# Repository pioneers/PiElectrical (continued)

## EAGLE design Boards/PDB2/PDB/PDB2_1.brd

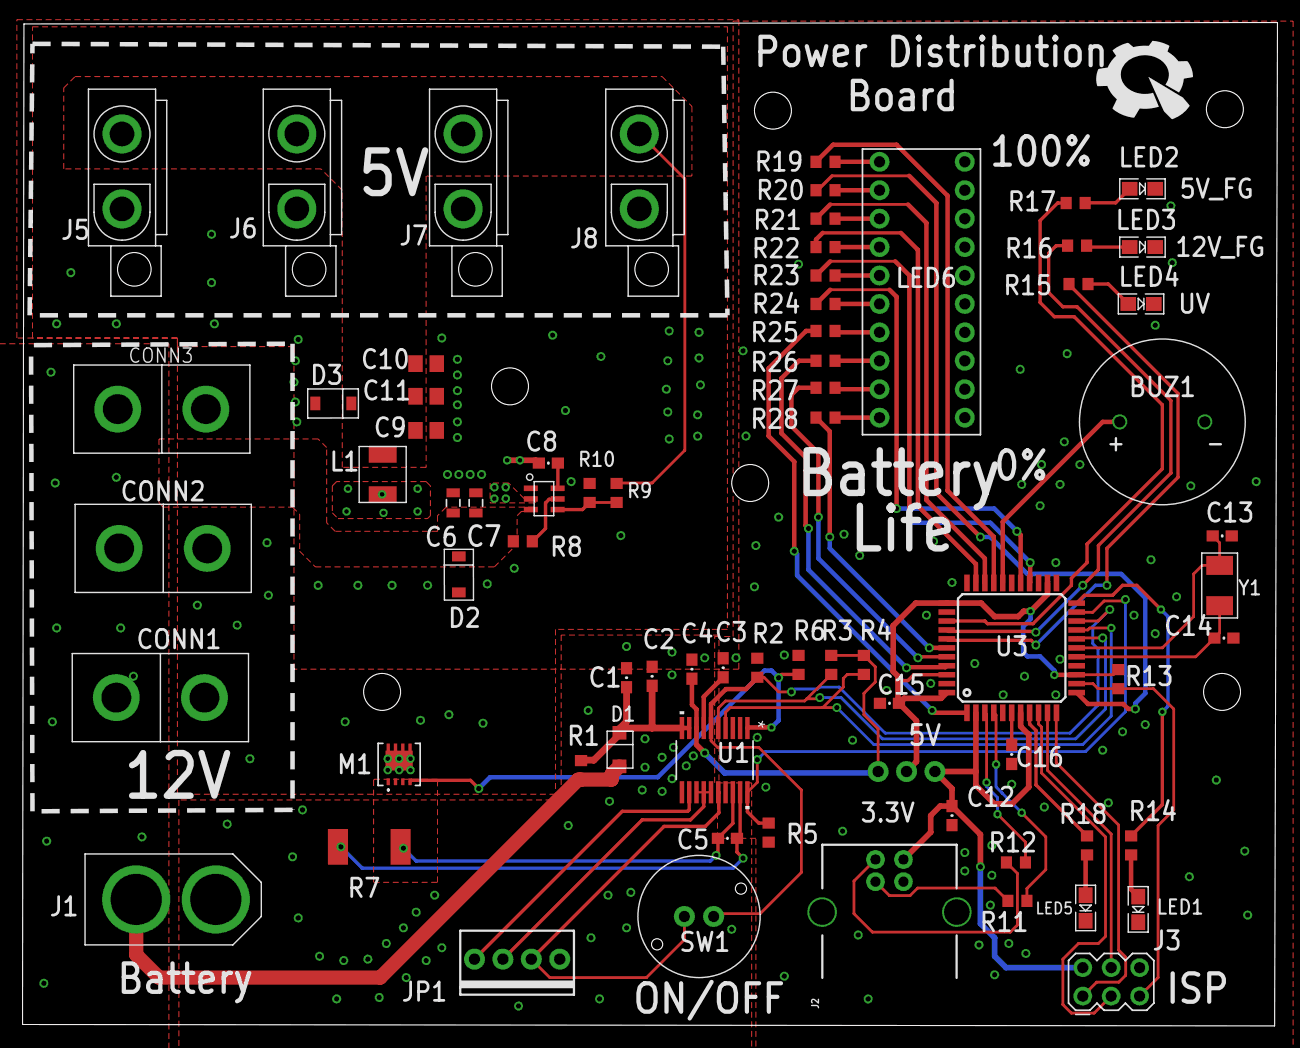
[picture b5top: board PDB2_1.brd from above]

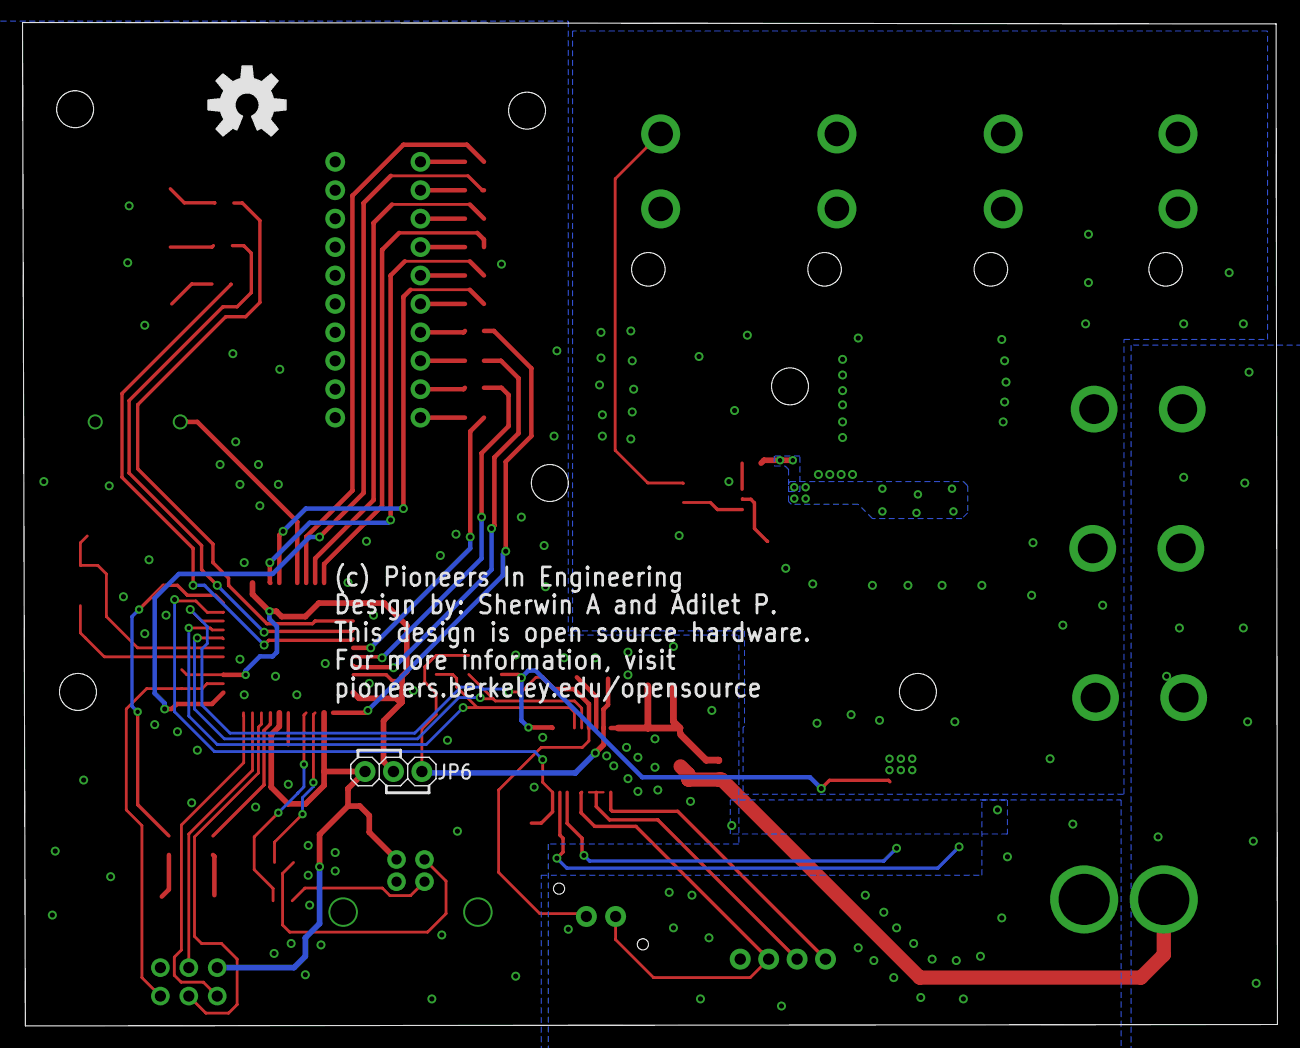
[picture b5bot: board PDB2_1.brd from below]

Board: 2 copper layers, 112.1 x 89.7 mm, 81 parts (2 on the bottom side), 64 nets.

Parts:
BUZ1: BUZZER_3.3V
C1, C2, C3, C4, C12, C15, C16: 2.2uF; 0603-CAP
C5, C8: .1uF; 0603-CAP
C6, C7: 22uF; 0805
C9, C10, C11: 22uF; C0805
C13, C14: 18pF; 0603-CAP
CONN1, CONN2, CONN3: ANDERSONVERTICAL; ANDERSON_VERTICAL
D1: D_NRVB120VLSFT1G; ON_SEMI_SOD-123F
D2, D3: BZT52C2VXX_ZENER; SOD-123
J1: XT60CONNECTOR
J2: USB_B_PTH; USB-B-PTH
J3: AVR_SPI_PRG_6MA03-2; MA03-2
JP1: 1X04-MTA
JP2, JP3, JP4, JP5: ATX
JP6: 1X03-JMP-OPTION
L1: 3.3uH; MWSA0402S
LED1, LED2, LED3, LED4, LED5: LED-0805
LED6: BAR_SEGMENT_DISPLAY
M1: CSD17577Q3A; DNH0008A
R1, R2, R8, R10, R13: 10k; R0603
R3, R4: 3.3k; R0603
R5, R6: 100k; R0603
R7: 5m; R2512
R9: 56.2k; R0603
R11, R12: 22R; R0603
R14, R15, R16, R17, R18: 330R; R0603
R19, R20, R21, R22, R23, R24, R25, R26, R27, R28: 220R; R0603
STANDOFF1, STANDOFF2, STANDOFF3, STANDOFF4, STANDOFF5, STANDOFF6: STAND-OFFTIGHT; STAND-OFF-TIGHT
SW1: PUSH_BUTTON; BUTTON_K12A
U1: BQ7692006PWRPW20-M; PW20-M
U2: SOT-23_6PIN_COPY
U3: ATMEGA32U4-AU; TQFP44
U$1: PIE-LOGO-SMALL
U$2: OSHW-LOGO-L
Y1: 8MHZ_X50328MSB2GI; SMD-5032_2P

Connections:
3.3V: C4.2, JP6.1, R3.2, R4.2, U1.8
5V: C9.1, C10.1, C11.1, D3.N, JP2.P$1, JP3.P$1, JP4.P$1, JP5.P$1, L1.P$1, R9.2
12V: C6.2, C7.2, CONN1.PIN1, CONN2.PIN2, CONN3.PIN2, D1.P, D2.N, J1.12V, R1.2, R8.1, U2.P$3
ALERT: R5.1, U1.20, U3.21
BCELL1: JP1.2, SW1.P$1, U1.16
BCELL2: JP1.3, U1.13, U1.14, U1.15
BCELL3: JP1.4, U1.12
BOOT: R2.2, SW1.P$2, U1.6, U3.20
BST: C8.1, U2.P$6
BUZZ: BUZ1.P1, U3.29
CAP1: C3.2, U1.7
D+: J2.D+, R11.1
D-: J2.D-, R12.1
DSG: M1.4, R6.2, U1.1
EN/MISO: J3.1, U3.11
FB: R9.1, R10.2, U2.P$4
GND: BUZ1.P2, C1.1, C2.1, C3.1, C4.1, C5.2, C12.1, C13.1, C14.1, C15.1, C16.1, J1.GND, J2.GND, J2.SHLD1, J2.SHLD2, J3.6, JP1.1, LED1.C, LED2.C, LED3.C, LED4.C, LED5.C, LED6.BAR_DISPLAY10, LED6.BAR_DISPLAY11, LED6.BAR_DISPLAY12, LED6.BAR_DISPLAY13, LED6.BAR_DISPLAY14, LED6.BAR_DISPLAY15, LED6.BAR_DISPLAY16, LED6.BAR_DISPLAY17, LED6.BAR_DISPLAY18, LED6.BAR_DISPLAY19, R2.1, R5.2, R6.1, R7.2, U1.3, U1.17, U1.19, U3.5, U3.15, U3.23, U3.33, U3.35, U3.43
GND_OUT: C6.1, C7.1, C9.2, C10.2, C11.2, CONN1.PIN2, CONN2.PIN1, CONN3.PIN1, D2.P, D3.P, JP2.P$2, JP3.P$2, JP4.P$2, JP5.P$2, M1.5, M1.6, M1.7, M1.8, M1.9, R10.1, U2.P$1
LED1: R28.1, U3.39
LED2: R27.1, U3.40
LED3: R26.1, U3.41
LED4: R25.1, U3.1
LED5: R24.1, U3.27
LED6: R23.1, U3.26
LED7: R22.1, U3.32
LED8: R21.1, U3.31
LED9: R20.1, U3.12
LED10: R19.1, U3.30
MOSI: J3.4, U3.10
unnamed: C13.2, U3.17, Y1.P$2
unnamed: R12.2, U3.3
unnamed: R11.2, U3.4
unnamed: C14.2, U3.16, Y1.P$1
unnamed: C16.2, U3.6
unnamed: LED6.BAR_DISPLAY0, R19.2
unnamed: LED6.BAR_DISPLAY1, R20.2
unnamed: LED6.BAR_DISPLAY2, R21.2
unnamed: LED6.BAR_DISPLAY3, R22.2
unnamed: LED6.BAR_DISPLAY4, R23.2
unnamed: LED6.BAR_DISPLAY5, R24.2
unnamed: LED6.BAR_DISPLAY6, R25.2
unnamed: LED6.BAR_DISPLAY7, R26.2
unnamed: LED6.BAR_DISPLAY8, R27.2
unnamed: LED6.BAR_DISPLAY9, R28.2
unnamed: R18.1, U3.8
unnamed: LED5.A, R18.2
unnamed: LED1.A, R14.2
unnamed: R14.1, U3.22
unnamed: R8.2, U2.P$5
unnamed: R17.1, U3.36
unnamed: R16.1, U3.37
unnamed: R15.1, U3.38
unnamed: LED2.A, R17.2
unnamed: LED3.A, R16.2
unnamed: LED4.A, R15.2
RST: J3.5, R13.1, U3.13
SCL: R3.1, U1.5, U3.18
SCLK: J3.3, U3.9
SDA: R4.1, U1.4, U3.19
SRP: C5.1, M1.1, M1.2, M1.3, R7.1, U1.18
SW: C8.2, L1.P$2, U2.P$2
UVCC: C12.2, J2.VBUS, J3.2, JP6.3, U3.2, U3.7
VCC: C15.2, JP6.2, R13.2, U3.14, U3.24, U3.34, U3.42, U3.44
VIN: C1.2, C2.2, D1.N, R1.1, U1.9, U1.10

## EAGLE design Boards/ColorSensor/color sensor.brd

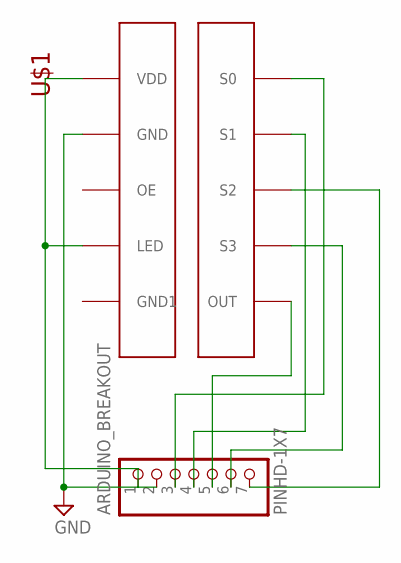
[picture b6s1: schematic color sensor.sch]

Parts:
ARDUINO_BREAKOUT: PINHD-1X7; 1X07
U$1: COLOR_SENSOR

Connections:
GND: ARDUINO_BREAKOUT.2, U$1.P9 (GND)
unnamed: ARDUINO_BREAKOUT.1, U$1.P7 (LED), U$1.P10 (VDD)
unnamed: ARDUINO_BREAKOUT.3, U$1.P5 (S0)
unnamed: ARDUINO_BREAKOUT.4, U$1.P4 (S1)
unnamed: ARDUINO_BREAKOUT.7, U$1.P3 (S2)
unnamed: ARDUINO_BREAKOUT.6, U$1.P2 (S3)
unnamed: ARDUINO_BREAKOUT.5, U$1.P1 (OUT)

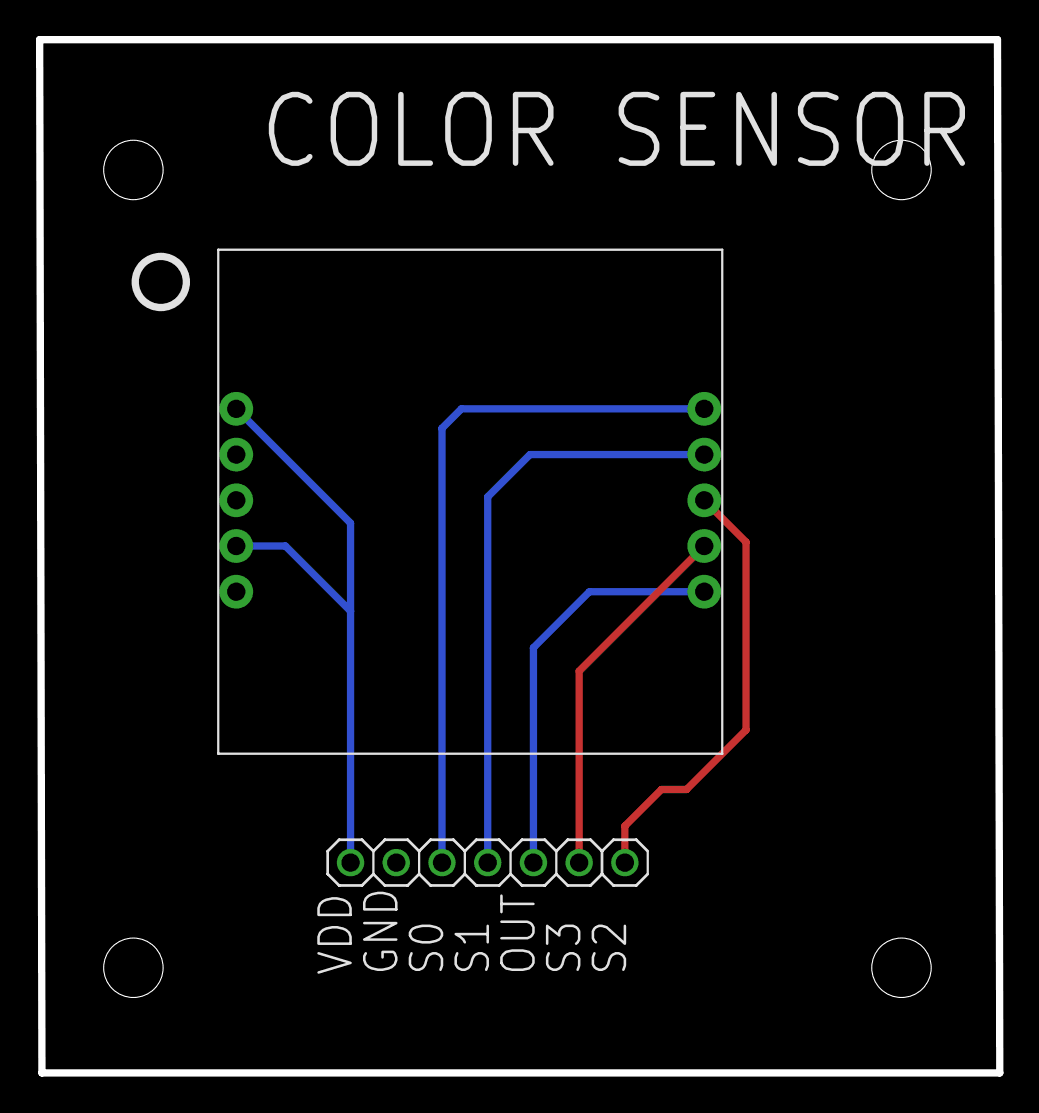
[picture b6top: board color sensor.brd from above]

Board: 2 copper layers, 53.3 x 57.4 mm, 7 parts (1 on the bottom side), 7 nets.

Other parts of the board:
U$2: PIE-LOGO
U$3, U$4, U$5, U$6: STAND-OFF

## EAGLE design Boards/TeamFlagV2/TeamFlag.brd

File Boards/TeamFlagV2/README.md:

# TeamFlag

* ~~make the holes where the USB goes in SMALLER~~
* ~~add "+" and "-" to those holes so u know what they r~~

REV B CHANGES NEEDED
* find a USB that we don't have to strip and is shorter

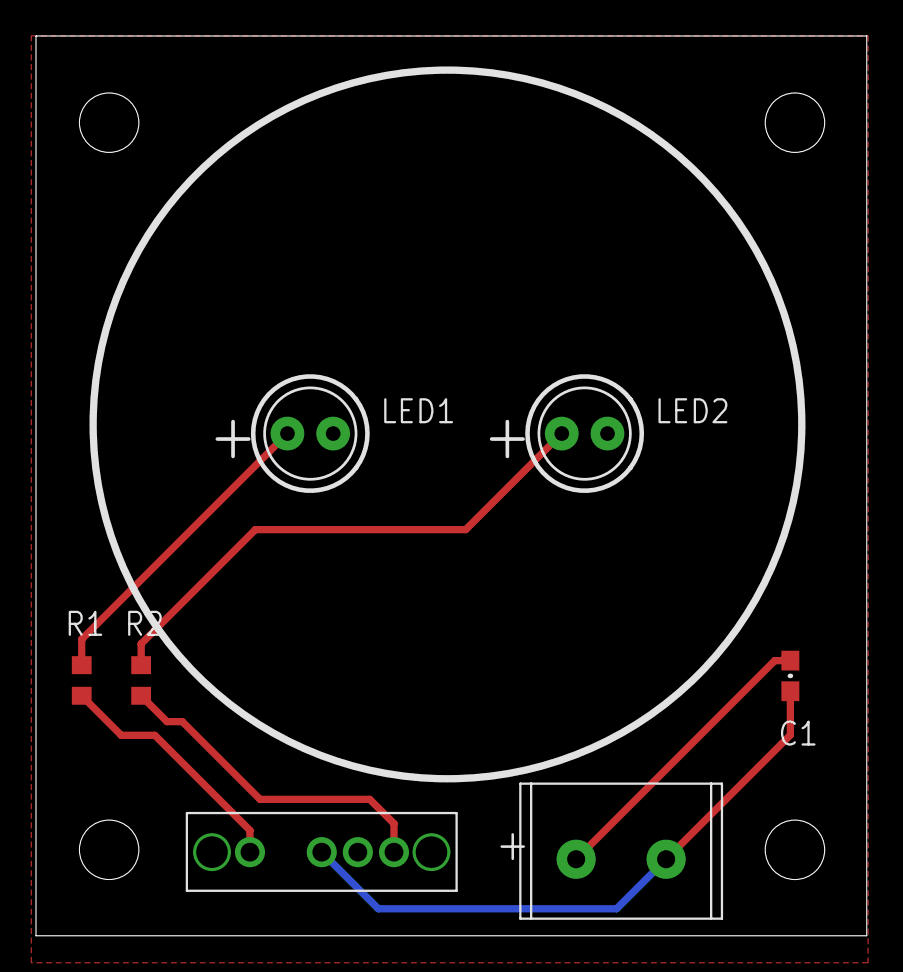
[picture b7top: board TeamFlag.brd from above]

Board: 2 copper layers, 46.2 x 50.0 mm, 12 parts (1 on the bottom side), 6 nets.

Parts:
C1: 0.1uF; 0603-CAP
LED1: Yellow; LED5MM-NOFLAT
LED2: Blue; LED5MM-NOFLAT
R1, R2: 130; R0603
ST1: 2PIN_SCREW
U$2: SP3T_SLIDE_SWITCH
U$3, U$4, U$5, U$6: STAND-OFF
U$7: PIE-LOGO-SMALL

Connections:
GND: C1.1, LED1.K, LED2.K, ST1.P$1
unnamed: LED1.A, R1.1
unnamed: LED2.A, R2.1
PIN1: R1.2, U$2.PIN1
PIN4: R2.2, U$2.PIN4
VCC: C1.2, ST1.P$2, U$2.PIN2

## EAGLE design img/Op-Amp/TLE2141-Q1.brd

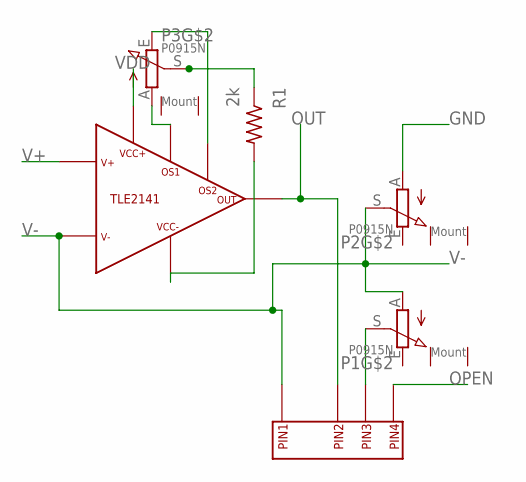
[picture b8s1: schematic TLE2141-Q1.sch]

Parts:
P1, P2, P3: P0915N
R1: 2k; 0207/15
U$1: TLE2141-Q1
U$2: SP3T_SLIDE_SWITCH

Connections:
GND: P2.A, R1.2, U$1.VCC- (VSS)
unnamed: P3.A, U$1.OFFSETN1 (OS1)
unnamed: P3.E, U$1.OFFSETN2 (OS2)
unnamed: P1.S, U$2.PIN3
unnamed: P3.S, R1.1
OPEN: U$2.PIN4
OUT: U$1.OUT (VOUT), U$2.PIN2
V+: U$1.IN+ (V+)
V-: P1.A, P2.S, U$1.IN- (V-), U$2.PIN1
VDD: U$1.VCC+ (VDD)

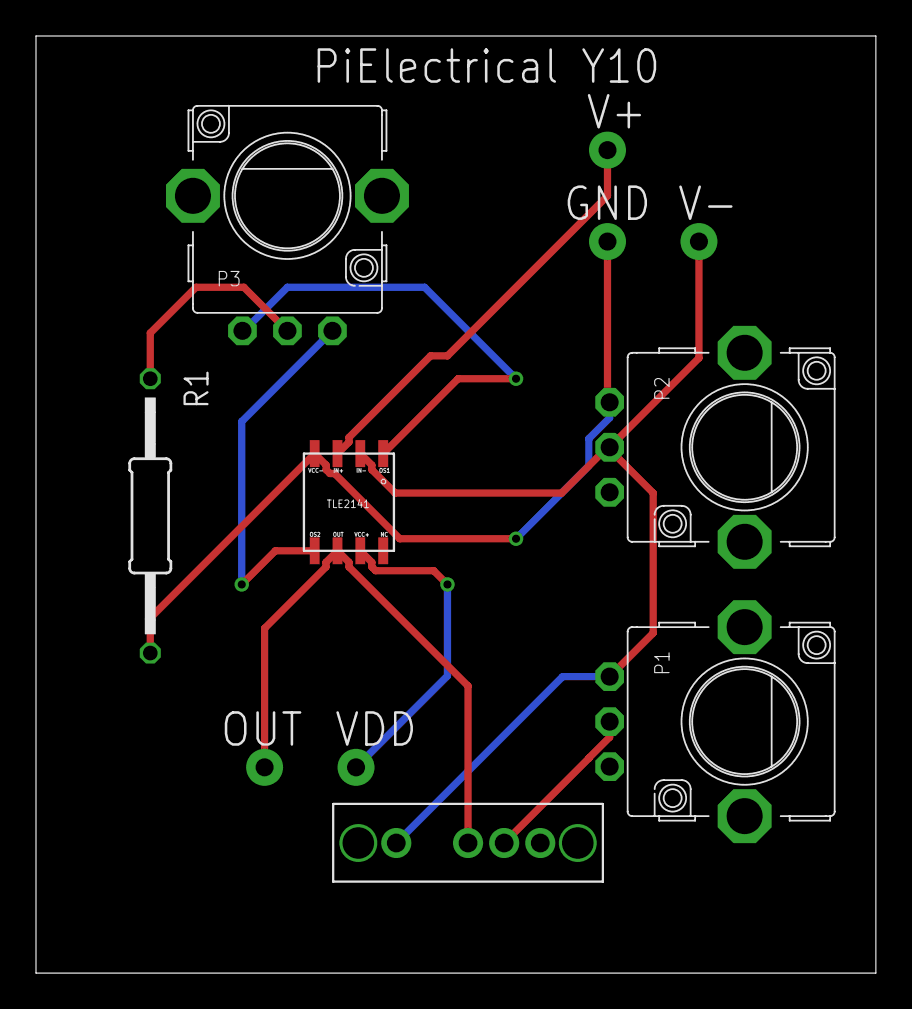
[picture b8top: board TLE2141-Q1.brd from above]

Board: 2 copper layers, 46.7 x 52.1 mm, 7 parts (1 on the bottom side), 7 nets.

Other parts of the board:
U$3: PIE-LOGO

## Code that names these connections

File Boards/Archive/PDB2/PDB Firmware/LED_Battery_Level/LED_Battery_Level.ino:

#include <bq769x0.h>

//LED mapping
#define LED1 A3
#define LED2 A4
#define LED3 A5
#define LED4 7
#define LED5 6
#define LED6 12
#define LED7 13
#define LED8 5
#define LED9 11
#define LED10 10


void battery_level(int level);

void setup() {
  pinMode(
}

void loop() {

  
}

void setup_segment_display() {
  pinMode(
}

void battery_level(int level) {
  if (level < 0 || level > 10) {
    return 0; 
  }
  else {
    for (int n=1; n<=10; n++){
      digitalWrite(n, LOW);
    }
    for (int i=1; i<=level; i++) {
      digitalWrite(i, HIGH);
    }
  }
}

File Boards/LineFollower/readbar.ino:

/*
    For a pair of sensors (A,B):
    Voltage > 3.5 -> Line under A
    Voltage < 1.5 -> Line under B
    Voltage ~= 2.5 -> Line under neither

    Distance between A and B: 2cm

    A   B   C   D   E   F
            --
*/


#define BAUD_RATE       9600
#define SENS_1          A1
#define STROBE_1        A0
#define IR_LED_2        A2
#define IR_LED_1        A3
#define IR_LED_3        15
#define CTRL_A          14
#define CTRL_B          16
#define STROBE_2        10

float vol1 = 0.0;
float vol2 = 0.0;
float vol3 = 0.0;

void setup() {
  Serial.begin(BAUD_RATE);

  // Setup the digital pins as outputs
  pinMode(STROBE_1, OUTPUT);
  pinMode(STROBE_2, OUTPUT);
  pinMode(IR_LED_2, OUTPUT);
  pinMode(IR_LED_1, OUTPUT);
  pinMode(IR_LED_3, OUTPUT);
  pinMode(CTRL_A, OUTPUT);
  pinMode(CTRL_B, OUTPUT);
  pinMode(SENS_1, INPUT);

  // Turn on the IR LEDs
  digitalWrite(IR_LED_1, HIGH);
  digitalWrite(IR_LED_2, HIGH);
  digitalWrite(IR_LED_3, HIGH);

  //Always reading so set strobe to low
  digitalWrite(STROBE_1, LOW);
  digitalWrite(STROBE_2, LOW);

  Serial.print("Setup Done");
}

void loop () {

  //read voltage differences between pairs of sensors
  vol1 = readPair(LOW, LOW); //TIA1 and TIA2
  Serial.println(vol1);
  vol2 = readPair(HIGH, LOW); //TIA3 and TIA4
  Serial.println(vol2);
  vol3 = readPair(LOW, HIGH); //TIA5 and TIA6
  Serial.println(vol3);
  
}

float readPair(const A, const B) {
  digitalWrite(CTRL_A, A);
  digitalWrite(CTRL_B, B);
  delay(1000);
  int sensorValue = analogRead(SENS_1);
  float voltage = sensorValue * (5.0 / 1023.0) ;
  return sensorValue;
}

float getPosition() {
    
}

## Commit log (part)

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2017-01-03 Update ATX conn and 5v Buck
2017-01-03 Update the ATX part and move around to fit board
2017-01-03 Renew the pdb gerb
2017-01-04 Update molex part
2017-01-05 Update molex to have name
2017-01-05 Update molex, remove old labels;
2017-01-06 Add silkscreen for andersons and molex
2017-01-06 Update revision and cam
2017-01-06 Add the production gerber
2017-01-07 Update PDB and Servo in PRD Gerb
2017-01-07 HOPEFULLY FINAL PROD GERB
2017-01-14 Migrate over Dougs docu-packet stuff
2017-01-14 Remove yaml and caption
2017-01-14 Add docu info
2017-01-17 Added top stencil to docu packet
2017-01-17 Fix scaling on laser stencil
2017-01-26 Improving README to reflect documentation changes
2017-01-28 adds status_lights_driver.py as modified from forseti2 to control field lights
2017-02-01 Fix drill hole sizes for 2,3,4 pin screw headers.
    If you're using these parts on your board, you'll need to update the library "Library -> Update All" to use this new part
2017-02-02 Controlling all lights from command line
2017-02-02 Add docu packets
2017-02-02 Add docu generating script
2017-02-03 Dank message
2017-02-03 Removed backups
2017-02-03 Made it better
2017-02-04 Added indexes to buttons which correspond to their master field light.
2017-02-04 bye bye main
2017-02-04 added the forbidden function
2017-02-04 Integrating lights with buttons!
2017-02-04 fixed formatting errors for Averal.
2017-02-04 UNLIMITED POWER
2017-02-04 Added buzzer support
2017-02-04 Finished product (disco still doesnt' work though. Or buzzers)
2017-02-04 Add FC RFID code
2017-02-08 I made the disco button actually functional.
2017-02-16 Add pullup resistors to encoders
2017-02-16 Adding Relay part
2017-02-18 Made it so it won't crash when you load images.
2017-02-18 Remove old status lights driver
2017-02-22 Add script info to README for docu packet generation
2017-02-23 Adding images for SmartSensor Wiki
2017-02-23 Adding images for SmartSensor Wiki (#68)
2017-02-23 More images
2017-02-23 Averal/wiki (#69)
    * Adding images for SmartSensor Wiki
    * More images
2017-03-09 pic for TeamFlag
2017-03-09 Averal/wiki (#72)
    * Adding images for SmartSensor Wiki
    * More images
    * pic for TeamFlag
2017-05-27 Reorganize and rename
2017-05-27 Update to use different directory
2017-05-27 Add Y9 Folder for archiving purposes
2017-05-27 Fix markdown
2017-05-27 Update Makefile
2017-05-27 Add PDB readme
2017-05-27 Add more documentation
2017-05-27 Add more todo and organize
2017-05-27 Reorganize archive
2017-05-27 Add my comments on all boards
2017-05-27 Add aravinds wisdom
2017-05-31 Move around images to one location
2017-05-31 Add eagle directories picture
2017-06-01 Update README.md
    beep boop
2017-06-01 Added Micro USB
2017-06-01 Added SPDT switch to lib
2017-06-01 Team flag schematic/board WIP
2017-06-02 Replaced SPDT with SP3T slide switch, and fixed teamflag v2
2017-06-02 Fixed some issues with SP3T switch and board layout
2017-06-07 Fixed clearence issues with the SP3T slide
2017-06-07 Merged libraries
2017-06-07 Fixed board with new part updates
2017-06-07 Appeasing the master
2017-06-07 swag eata that averal
2017-06-10 Added comments to boards
    and also fixed grammer mistakes.
2017-06-11 Added comments to boards (#78)
    Thanks Doug
2017-07-02 I don't know
2017-07-02 Added the MUX and the OP amp. also imported the DIP 8 and 16 pin packages
2017-07-02 Deleted old team flag from main folder. It still exists in Y9 folder
2017-07-08 Fix the routing issues
2017-07-31 Change pullup resistor vcalue
2017-07-31 Add gain for antenna
2017-08-19 team flag fixed <3 margo
2017-08-19 fixed a thing in team flag
2017-08-26 PMW in motor controller to PWM
2017-08-31 ayy lmao
2017-08-31 REEEEEEEEEEEEEEEEEEEEEEEEEEEEEEEEEEEEEEEEEEEEEEEEE ADDED SOT23-6pin REEEEEEEEEEEEEEEEEEEEEEEEEEEEEEEEEEE
2017-09-01 ggetting caught up
2017-09-01 SO MUCH
2017-09-01 Forgot to power the op amp
2017-09-07 Started routing
2017-09-07 Semi done routing
2017-09-07 Finished
2017-09-07 Got rid of warning error when opening library
2017-09-07 Fixed a 90 deg angle
2017-09-09 add test file and documentation for line break sensor
2017-09-09 Readd the piecam
2017-09-16 Add testing procedure
2017-09-21 Labeled Servos correctly and changed rev cycle
2017-09-21 Updated Rev on frames (does not necessarily mean that everything is good-to-go)
2017-09-21 Rerouted EN to A3 from 14
2017-09-23 cronCH
2017-09-23 rev a is a gogo
2017-10-05 Create TeamFlag
2017-10-07 made hole guys smaller for usb and labeled positive one
2017-10-14 margo moved the arduino slightly to the left so it doesn't touch the hole guy
2017-10-14 Added test code for test board
2017-10-14 more ocd alignment changes
2017-10-14 fixed the actual thing seiya wanted -- moved the arduino(?) to the middle between the pillar/hole things
2017-10-14 actually actually fixed the thing seiya wanted -- the arduino is centered and the rfid is correctly moved -- also hopefully the drill hole matches up with the other thing (top right corner)
2017-10-15 rev 10b done, dfm all good2go
2017-10-15 REV B PLEASE WORK
2017-10-19 changed pull-ups to 10k my d00d
2017-10-28 Added back 5V buck and added caps. DRC clean
2017-11-02 Please, PDB, please work. Also I updated ATX connector.
2017-11-09 vital important work changing rev to prod i am a very significant part of this team -- team flag
2017-11-09 Updated revision names
2017-11-09 Updated Revision Name
2017-11-09 I hate my life
2017-11-30 Created Distance Sensor
2018-01-27 Board up
2018-01-27 Finish solar scramble
2018-01-28 Make some changes
2018-01-29 Finish up board
2018-02-10 add pulldown labels
2018-06-30 Added resistor array
2018-07-04 Modified resistor array part
2018-07-07 Created new 5PIN part to replace screw terminal
2018-07-07 add solder jumper part
2018-07-08 Created rough version of sensor board, split from TwistIt
2018-07-10 Revised SensorBoard and fixed TwistIt
2018-07-15 Split motor controller from TwistIt and modified resistor array to account for size errors
2018-07-21 Modified motor controller board
2018-07-21 add mc chip
2018-07-21 Created new radial electrolytic capacitor
2018-07-26 Completed rough version of motor controller chip board
2018-07-26 Finished prototype board
2018-07-26 Fixed font style for some text
2018-07-27 Centered board and added board name
2018-09-02 Added mc chip to motor controller board
2018-09-06 made directory for PDB battery management project
2018-09-06 Finished prototype of motor controller board
2018-09-06 Fixed LED color values not showing up
2018-09-29 Modifying motor controller
2018-09-29 Rev B Motor Controller
2018-10-07 added protoboard files and code for testing
2018-10-13 completed code for BQ76920 library and wrote tests
2018-10-21 made protoboard 2 for BQ76920
2018-10-27 Fixed routing to arduino pins
2018-10-27 Fixing sizes
2018-10-27 Created gerbs
2018-11-03 added final rev2 protoboard for BQ76920
2018-12-06 Modified tcream layer for reflowing
2018-12-10 PDB tcream for reflowing
2019-03-16 Miscellaneous
2019-04-13 shift register
2019-04-20 add a better mc33926 footprint and schematic
2019-04-25 started board
2019-04-27 board
2019-04-27 finished board routing ish
2019-06-23 start 6-motor controller project
2019-06-27 make and organize schematic for MCDB
2019-07-10 added atmega328pb-au to lib
2019-07-11 no more ignore pie.lbr
2019-07-11 ending...
2019-07-11 hopefully didn't break pie.lbr
2019-07-11 Started process of using new MC symbol
2019-07-11 yeet that lib
2019-07-13 Modified MC33926 part
2019-07-13 Started modifying motor controller board
2019-07-14 pdb layout and added parts to library
2019-07-14 finished rev1 pdb:
2019-07-14 yeet
2019-07-18 Added new MC part for the third time
2019-07-18 edited to accomodate new symbol
2019-07-18 add 32U4 to mcdb schematic
2019-07-20 Added atmega32u4 to library
2019-07-20 added new crystal footprint
2019-07-20 continued work on MCDB
2019-07-25 connected remaining pins on 32U4, added USB B and USB Micro
2019-07-25 added many capacitors (to USB D lines, to digital logic VCC for each MC, and three to VPWR)
2019-07-29 starting pdb rev2
2019-08-01 start working on animatronic
2019-08-01 sherwin's stupid fun adventure
2019-08-08 Continued layout of MCDB
2019-08-15 goddamn u sherwin; also deleted one unnecessary polygon
2019-08-15 tried routing some signals from MCU
2019-08-23 finished PDB, motorcontroller test board, and updates to pie lib
2019-08-24 Slight modification
2019-09-26 just pdb things
2019-11-02 Working on new motor controller
2019-11-02 Fixing conflicts
2019-11-02 Continued working on new motor controller
2019-11-03 Continuing work
2019-11-03 fixerd
2019-11-03 Rev A
2019-11-05 thweou th
2019-11-05 isp pls
2019-11-05 Routed the ISP Connector
2019-11-05 things
2019-11-07 added example
2019-11-14 Print cell voltages and time
2019-11-16 ultrasonic_ir board
2019-11-16 Gerb file for motor controller v2
2019-11-16 Fixing merge conflicts
2019-11-16 Fixing more errors in library
2019-11-17 fixed silkscreen fonts and ground pins
2019-11-26 usir files
2019-11-27 Rev B of the TI motor controller
2019-11-28 trerewrewr
2019-12-05 lets goo
2019-12-05 Removed code relating to bmic
2019-12-05 team flag screw terminal
2019-12-05 yeey
2019-12-05 fixed lib
2019-12-21 Modified encoder labelling
2019-12-27 Added heartbeat, rx leds
2019-12-27 Slightly modified motor controller
2019-12-27 Generated gerbers for production
2019-12-27 gerbs
2019-12-27 fixed pdb drc
2020-02-13 Added color sensor symbol
2020-02-15 Printout for PDB
2020-02-16 added arduino bootloadr flashing package
2020-02-20 Color sensor day 2
2020-02-20 color sensor cam job
2020-02-22 Color sensor gerb
2020-06-27 Added new motor controller
2020-06-27 ultrasonic
2020-06-27 add drv8872 library
2020-08-29 did the pcb stuff for the distancce sensor
2020-09-03 it all works now finally, (ultrasonic ir boards)
2020-11-28 please no mere conflict
2020-12-27 line follower schematic
2021-01-21 added mux to line follower
2021-01-30 lf updates
2021-01-30 adding 1st2020mc brd/sch
2021-02-04 more updates
2021-02-06 line follower done, code added
2021-02-07 2020mc v2
2021-02-13 catching up
2021-02-13 fixmylife
2021-02-13 maybe fixed
2021-02-18 2/17 mc2020 update
2022-03-31 Create Test
2022-03-31 Create blah
2022-03-31 Update blah
2023-08-26 adding PiEDB Y15 files
2023-08-29 testing image height
2023-08-29 added setup image for testing
2023-08-29 testing images again with correct filenames
2023-08-29 one last time... picture should work
2023-08-29 testing expandable sections
2023-08-29 added insructions to setup KiCad and symbol library
2023-08-29 Moved old eagle src files into hidden directory
2023-08-29 Moved some fabrication files and libraries
2023-08-29 trying larger collapsible sectoin
2023-08-29 trying again
2023-08-29 and again
2023-08-29 nah collapsible looks bad on large sections
2023-10-05 Re-organized folders and files
2023-10-05 updated structure section
2023-10-06 Committing Y15 PDB
2023-10-06 added kicad backup files to gitignore
2023-10-06 fix images
2023-10-20 Add images to tutorial
2023-10-21 update PDB to new version of kicad
2024-01-21 modified gitignore
2024-01-21 put new PDB in boards
2024-01-21 roughly finished layout for new dc-dc converter
2024-01-21 add new footprints TPS56C230RJER
2024-01-27 added mc chip footprint and symbol
2024-01-27 servo contoller
2024-01-29 updated BOM
2024-02-01 finished servo layout
2024-02-02 Ordered Servo Controller
2024-02-03 Worked on PDB Revision
2024-02-06 pictures of layout
2024-02-24 Revision of PDB
2024-03-10 Make new test board
2024-03-11 Added to do for PDB
2024-03-11 added 3d model for promicro
2024-03-16 made new PDB prototype
2024-03-16 added to-do
2024-04-11 Starting Revamp of MC
2024-04-25 atmega328p_prototype
2024-04-26 Created TTL Converter
2024-04-26 Put TTL Converter in correct folder
2024-06-07 PDB Updates
2024-06-07 added simon says and ultrasonic
2024-09-14 updated library: (BS-7) battery, TLC555 (timer)
2024-09-14 added Y16_motorControllerConversion project files
2024-09-14 starting onboarding
2024-09-14 updated TurboPDB schematic
2024-09-21 updated TurboPCB schematic and footprint; incomplete connector socket footprint assignment
2024-10-12 added 1mm through-hole pad to PiE footprint library for onboarding. Finished onboarding footprint.
2024-10-12 added turbo dxf files for onboarding footprint
2024-11-21 Added TCS230
2025-01-30 created PDB files from KiCad
